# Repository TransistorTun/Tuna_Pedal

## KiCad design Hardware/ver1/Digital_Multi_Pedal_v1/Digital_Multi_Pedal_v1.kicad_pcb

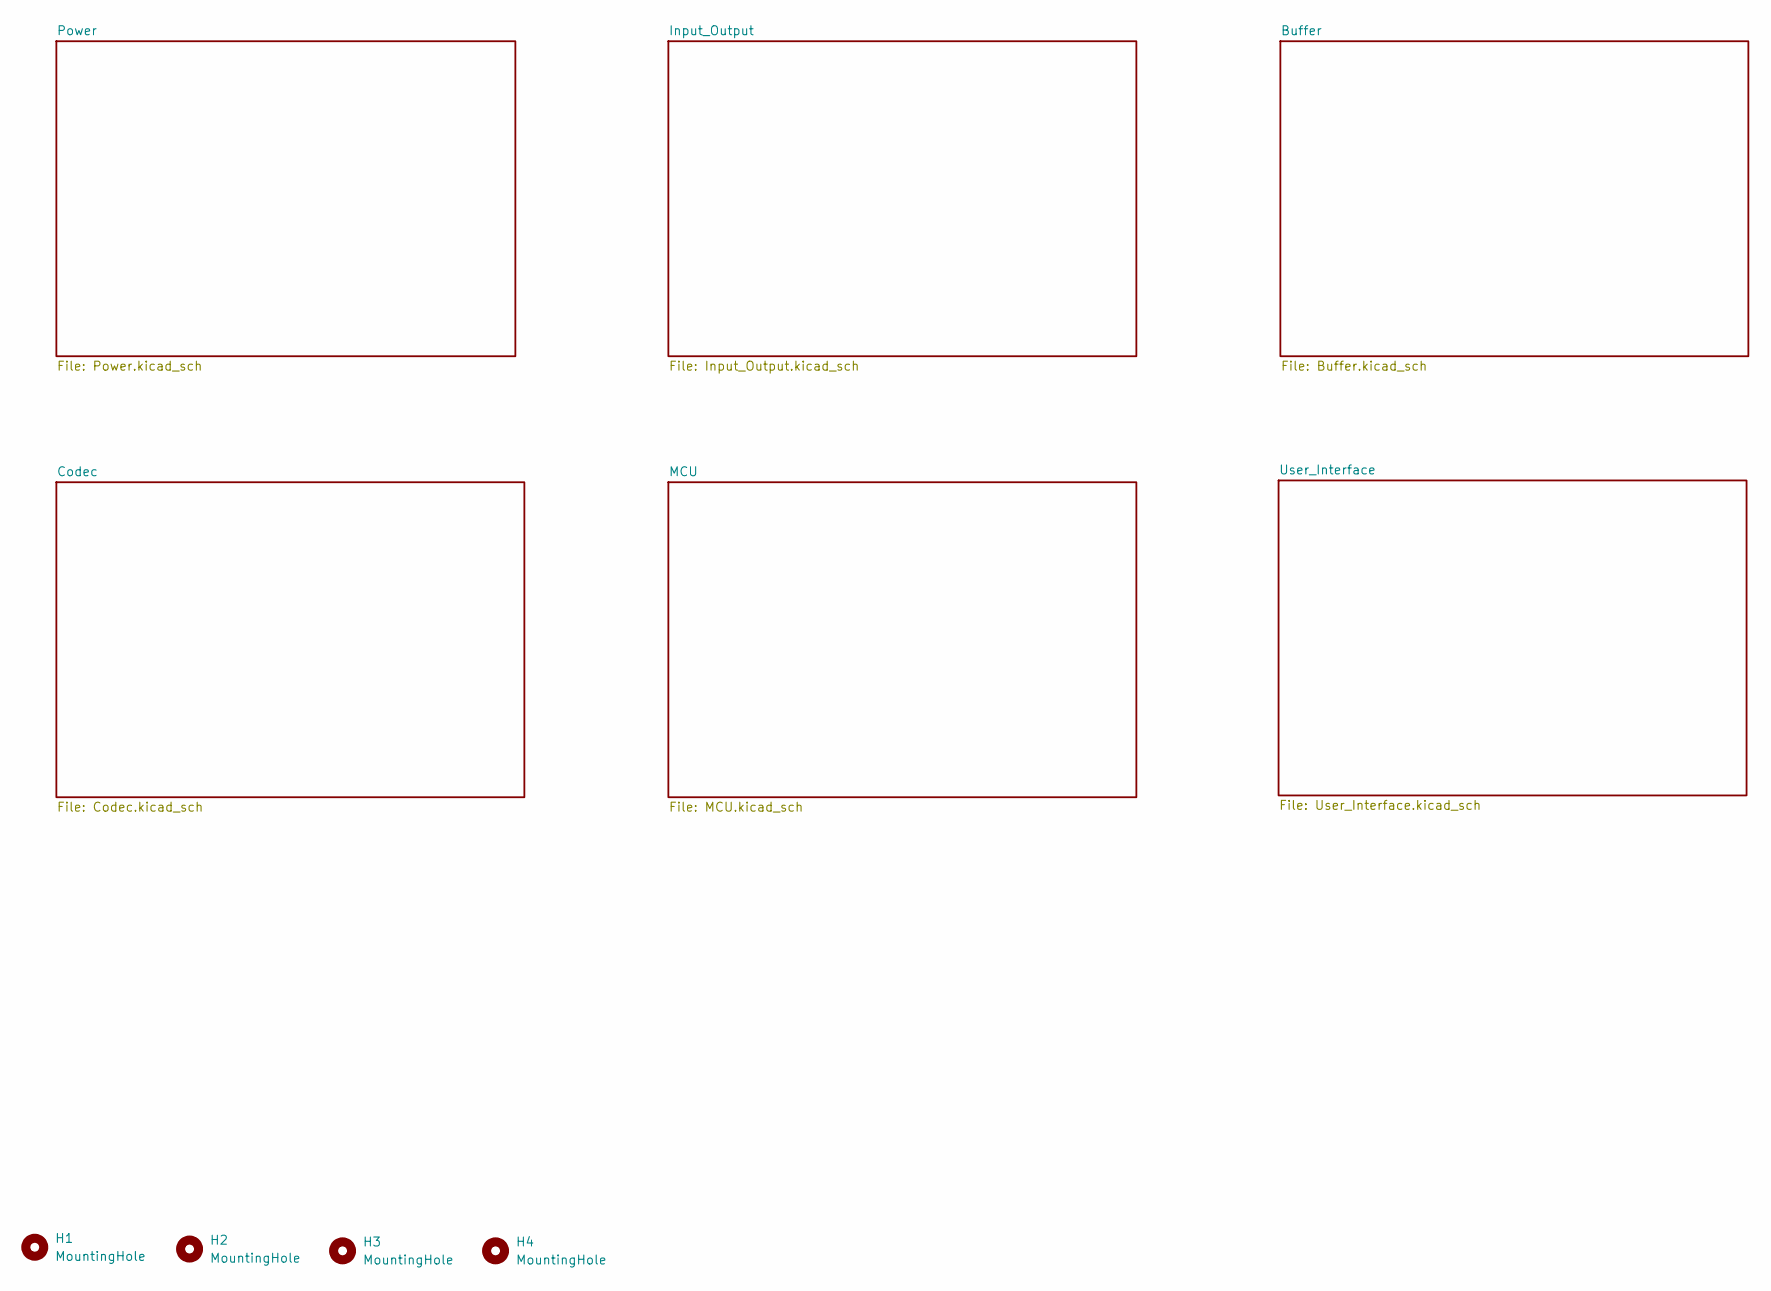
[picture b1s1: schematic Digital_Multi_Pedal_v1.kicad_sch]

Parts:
H1, H2, H3, H4: MountingHole; MountingHole_3.2mm_M3_Pad_Via

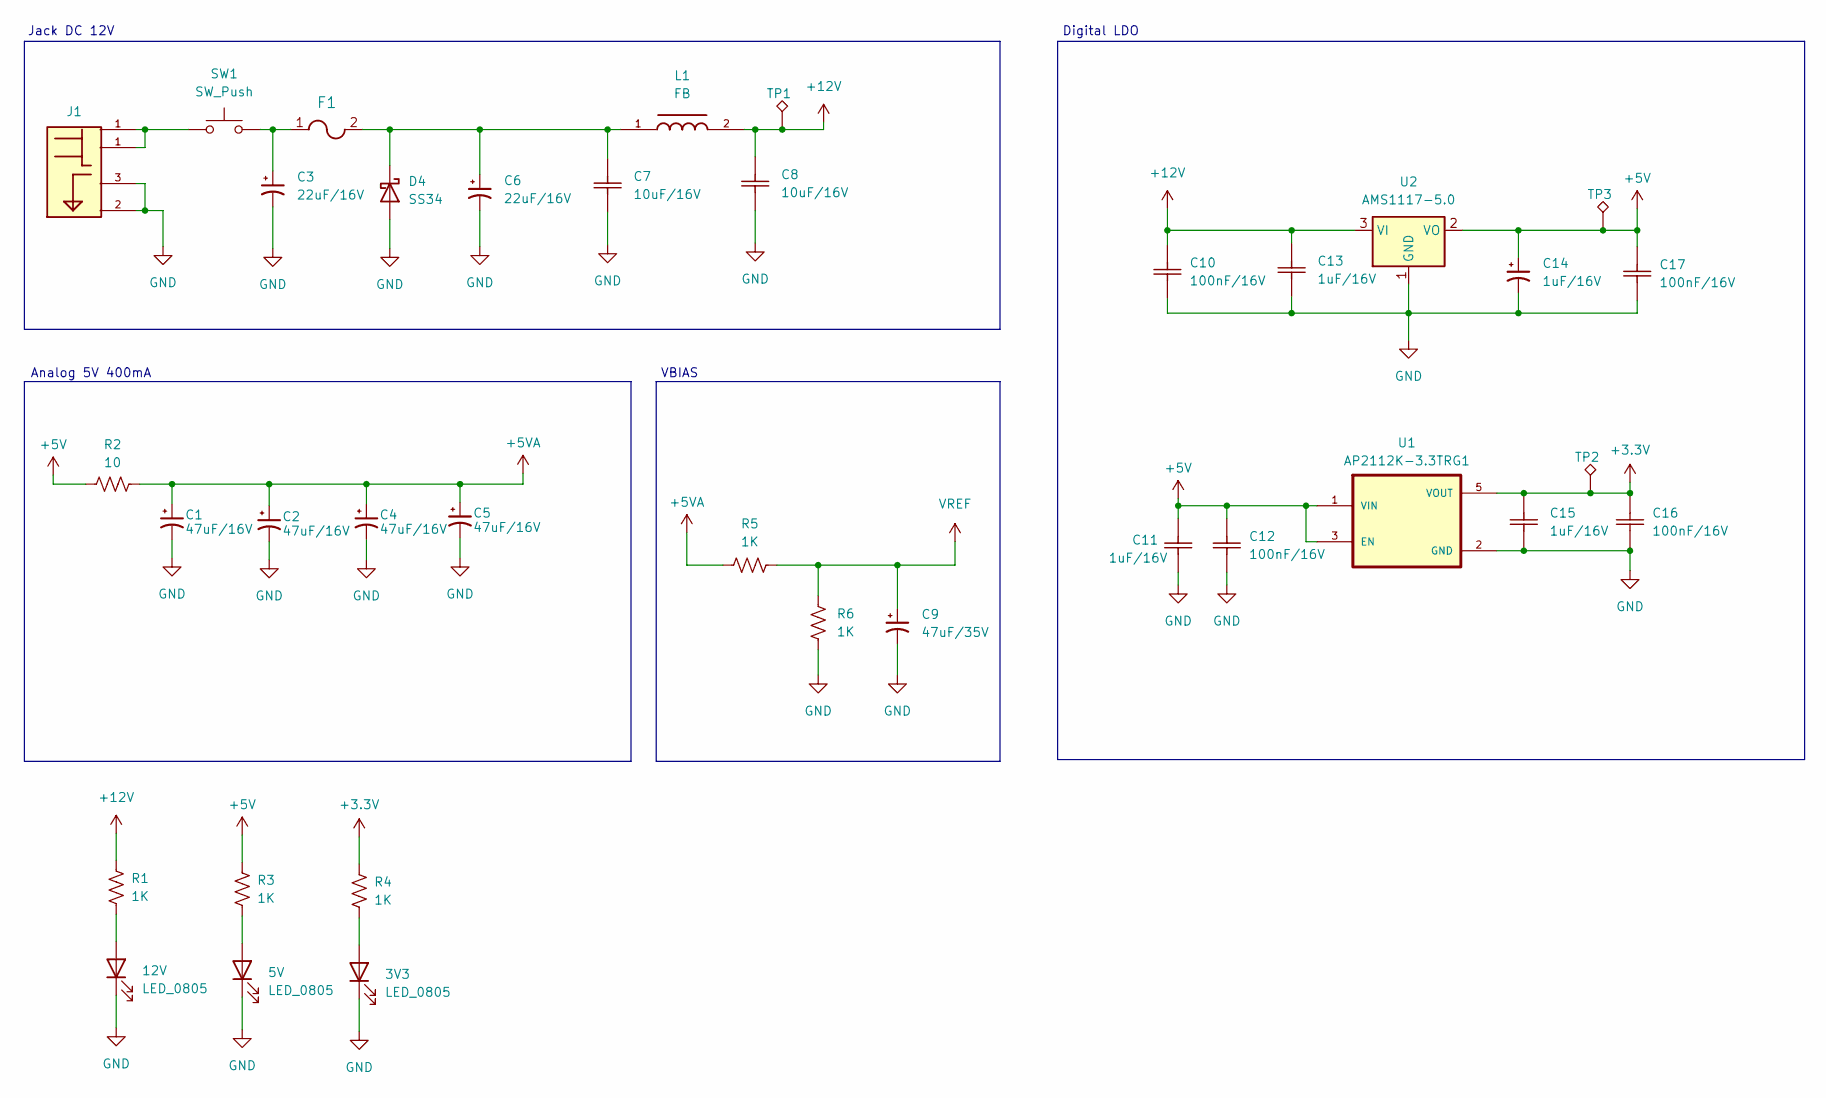
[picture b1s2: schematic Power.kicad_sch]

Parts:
3V3, 5V, 12V: LED_0805
C1, C2, C4, C5: 47uF/16V; Tan_Cap_C
C3, C6: 22uF/16V; Tan_Cap_A
C7, C8: 10uF/16V; Ceramic_Cap_0603
C9: 47uF/35V; Tan_Cap_C
C10, C12, C16, C17: 100nF/16V; Ceramic_Cap_0603
C11, C13, C15: 1uF/16V; Ceramic_Cap_0603
C14: 1uF/16V; Tan_Cap_A
D4: SS34; D_SMA
F1: Fuse; FUSE_1812L_LTF
J1: DCJ200-05-A-XX-X_REVA; JackDC
L1: FB; FB_0805
R1, R3, R4, R5, R6: 1K; Res_0603
R2: 10; Res_0603
SW1: SW_Push; Header_PW_Switch
TP1, TP2, TP3: TestPoint_Alt; TestPoint_Pad_D1.5mm
U1: AP2112K-3.3TRG1; SOT23; PARTREV 2-2
U2: AMS1117-5.0; SOT-223-3_TabPin2

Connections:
+3.3V: C15.2, C16.2, R4.1, TP2.1, U1.5 (VOUT); also elsewhere on the board
+5V: C11.2, C12.2, C14.1, C17.2, R2.2, R3.1, TP3.1, U1.1 (VIN), U1.3 (EN), U2.2 (VO); also elsewhere on the board
+5VA: C1.1, C2.1, C4.1, C5.1, R2.1, R5.2; also elsewhere on the board
+12V: C8.2, C10.2, C13.2, L1.2, R1.1, TP1.1, U2.3 (VI)
GND: 3V3.1 (K), 5V.1 (K), 12V.1 (K), C1.2, C2.2, C3.2, C4.2, C5.2, C6.2, C7.1, C8.1, C9.2, C10.1, C11.1, C12.1, C13.1, C14.2, C15.1, C16.1, C17.1, D4.2 (A), J1.2, J1.3, R6.1, U1.2 (GND), U2.1 (GND); also elsewhere on the board
unnamed: C3.1, F1.1, SW1.2
unnamed: 12V.2 (A), R1.2
unnamed: 5V.2 (A), R3.2
unnamed: 3V3.2 (A), R4.2
unnamed: C6.1, C7.2, D4.1 (K), F1.2, L1.1
unnamed: J1.1, SW1.1
VREF: C9.1, R5.1, R6.2; also elsewhere on the board

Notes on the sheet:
VBIAS
Jack DC 12V
Analog 5V 400mA
Digital LDO

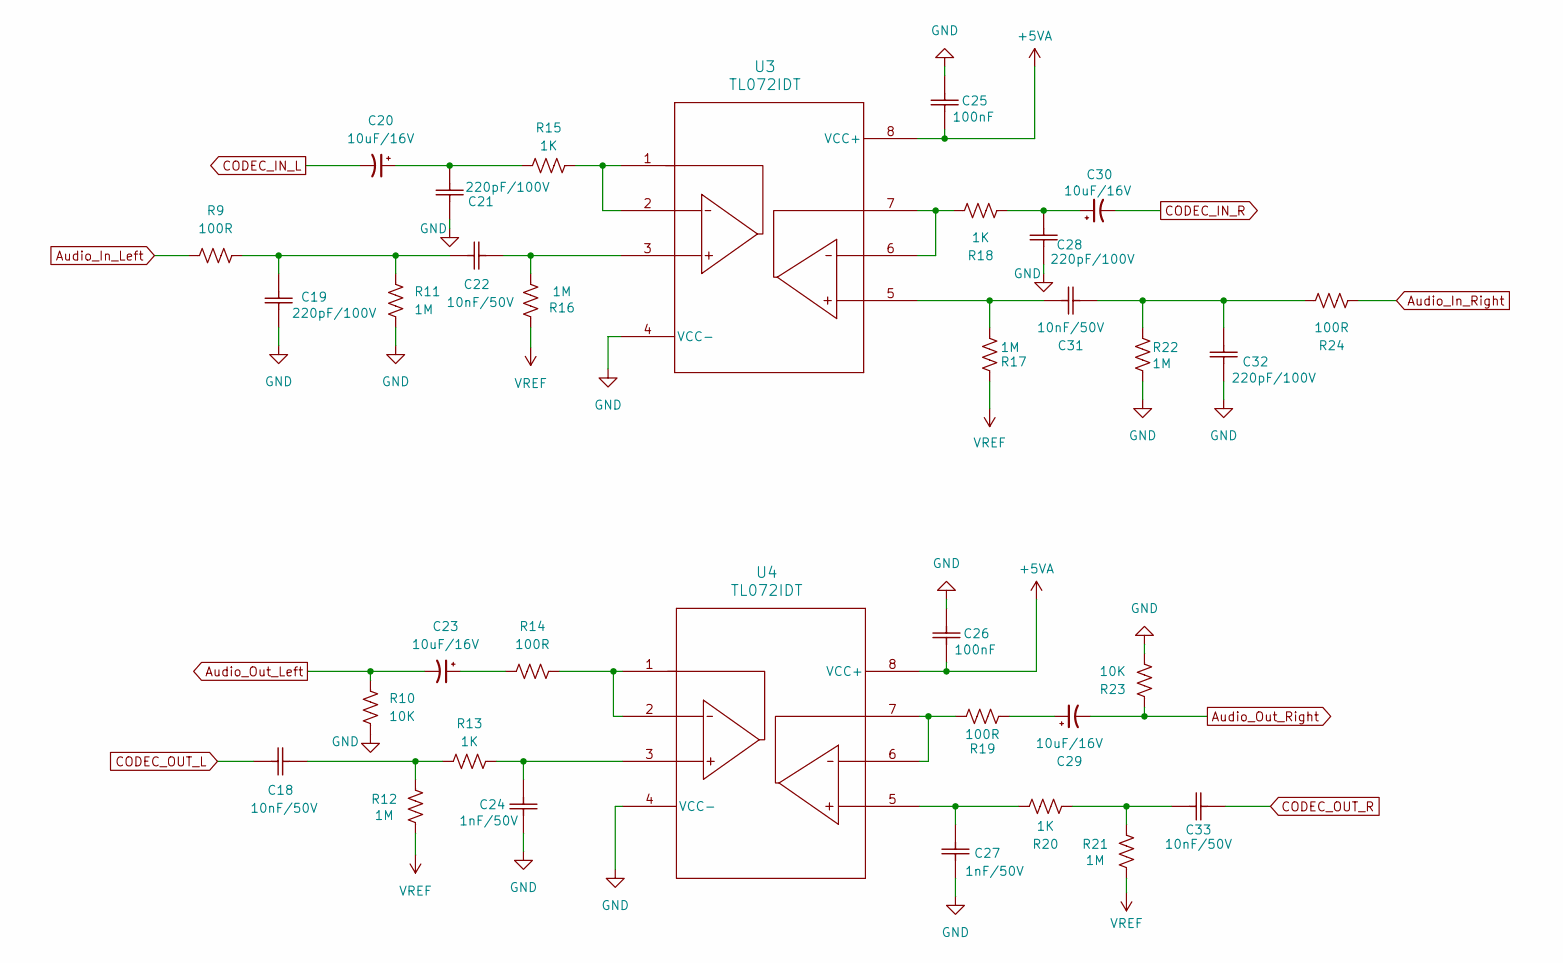
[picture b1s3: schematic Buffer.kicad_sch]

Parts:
C18, C22, C31, C33: 10nF/50V; Ceramic_Cap_0603
C19, C21, C28, C32: 220pF/100V; Ceramic_Cap_0603
C20, C23, C29, C30: 10uF/16V; Tan_Cap_A
C24, C27: 1nF/50V; Ceramic_Cap_0603
C25, C26: 100nF; Ceramic_Cap_0603
R9, R14, R19, R24: 100R; Res_0603
R10, R23: 10K; Res_0603
R11, R12, R16, R17, R21, R22: 1M; Res_0603
R13, R15, R18, R20: 1K; Res_0603
U3, U4: TL072IDT; D8_STM

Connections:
+5VA: C25.2, C26.2, U3.8 (VCC+), U4.8 (VCC+); also elsewhere on the board
Audio_In_Left: R9.1; also elsewhere on the board
Audio_In_Right: R24.1; also elsewhere on the board
Audio_Out_Left: C23.2, R10.2; also elsewhere on the board
Audio_Out_Right: C29.2, R23.2; also elsewhere on the board
CODEC_IN_L: C20.2; also elsewhere on the board
CODEC_IN_R: C30.2; also elsewhere on the board
CODEC_OUT_L: C18.1; also elsewhere on the board
CODEC_OUT_R: C33.1; also elsewhere on the board
GND: C19.2, C21.2, C24.1, C25.1, C26.1, C27.1, C28.2, C32.2, R10.1, R11.1, R22.1, R23.1, U3.4 (VCC-), U4.4 (VCC-); also elsewhere on the board
unnamed: C18.2, R12.2, R13.1
unnamed: C19.1, C22.1, R9.2, R11.2
unnamed: C20.1, C21.1, R15.1
unnamed: C22.2, R16.1, U3.3
unnamed: C23.1, R14.1
unnamed: C24.2, R13.2, U4.3
unnamed: C27.2, R20.2, U4.5
unnamed: C28.1, C30.1, R18.1
unnamed: C29.1, R19.1
unnamed: C31.1, C32.1, R22.2, R24.2
unnamed: C31.2, R17.1, U3.5
unnamed: C33.2, R20.1, R21.2
unnamed: R14.2, U4.1, U4.2
unnamed: R15.2, U3.1, U3.2
unnamed: R18.2, U3.6, U3.7
unnamed: R19.2, U4.6, U4.7
VREF: R12.1, R16.2, R17.2, R21.1; also elsewhere on the board

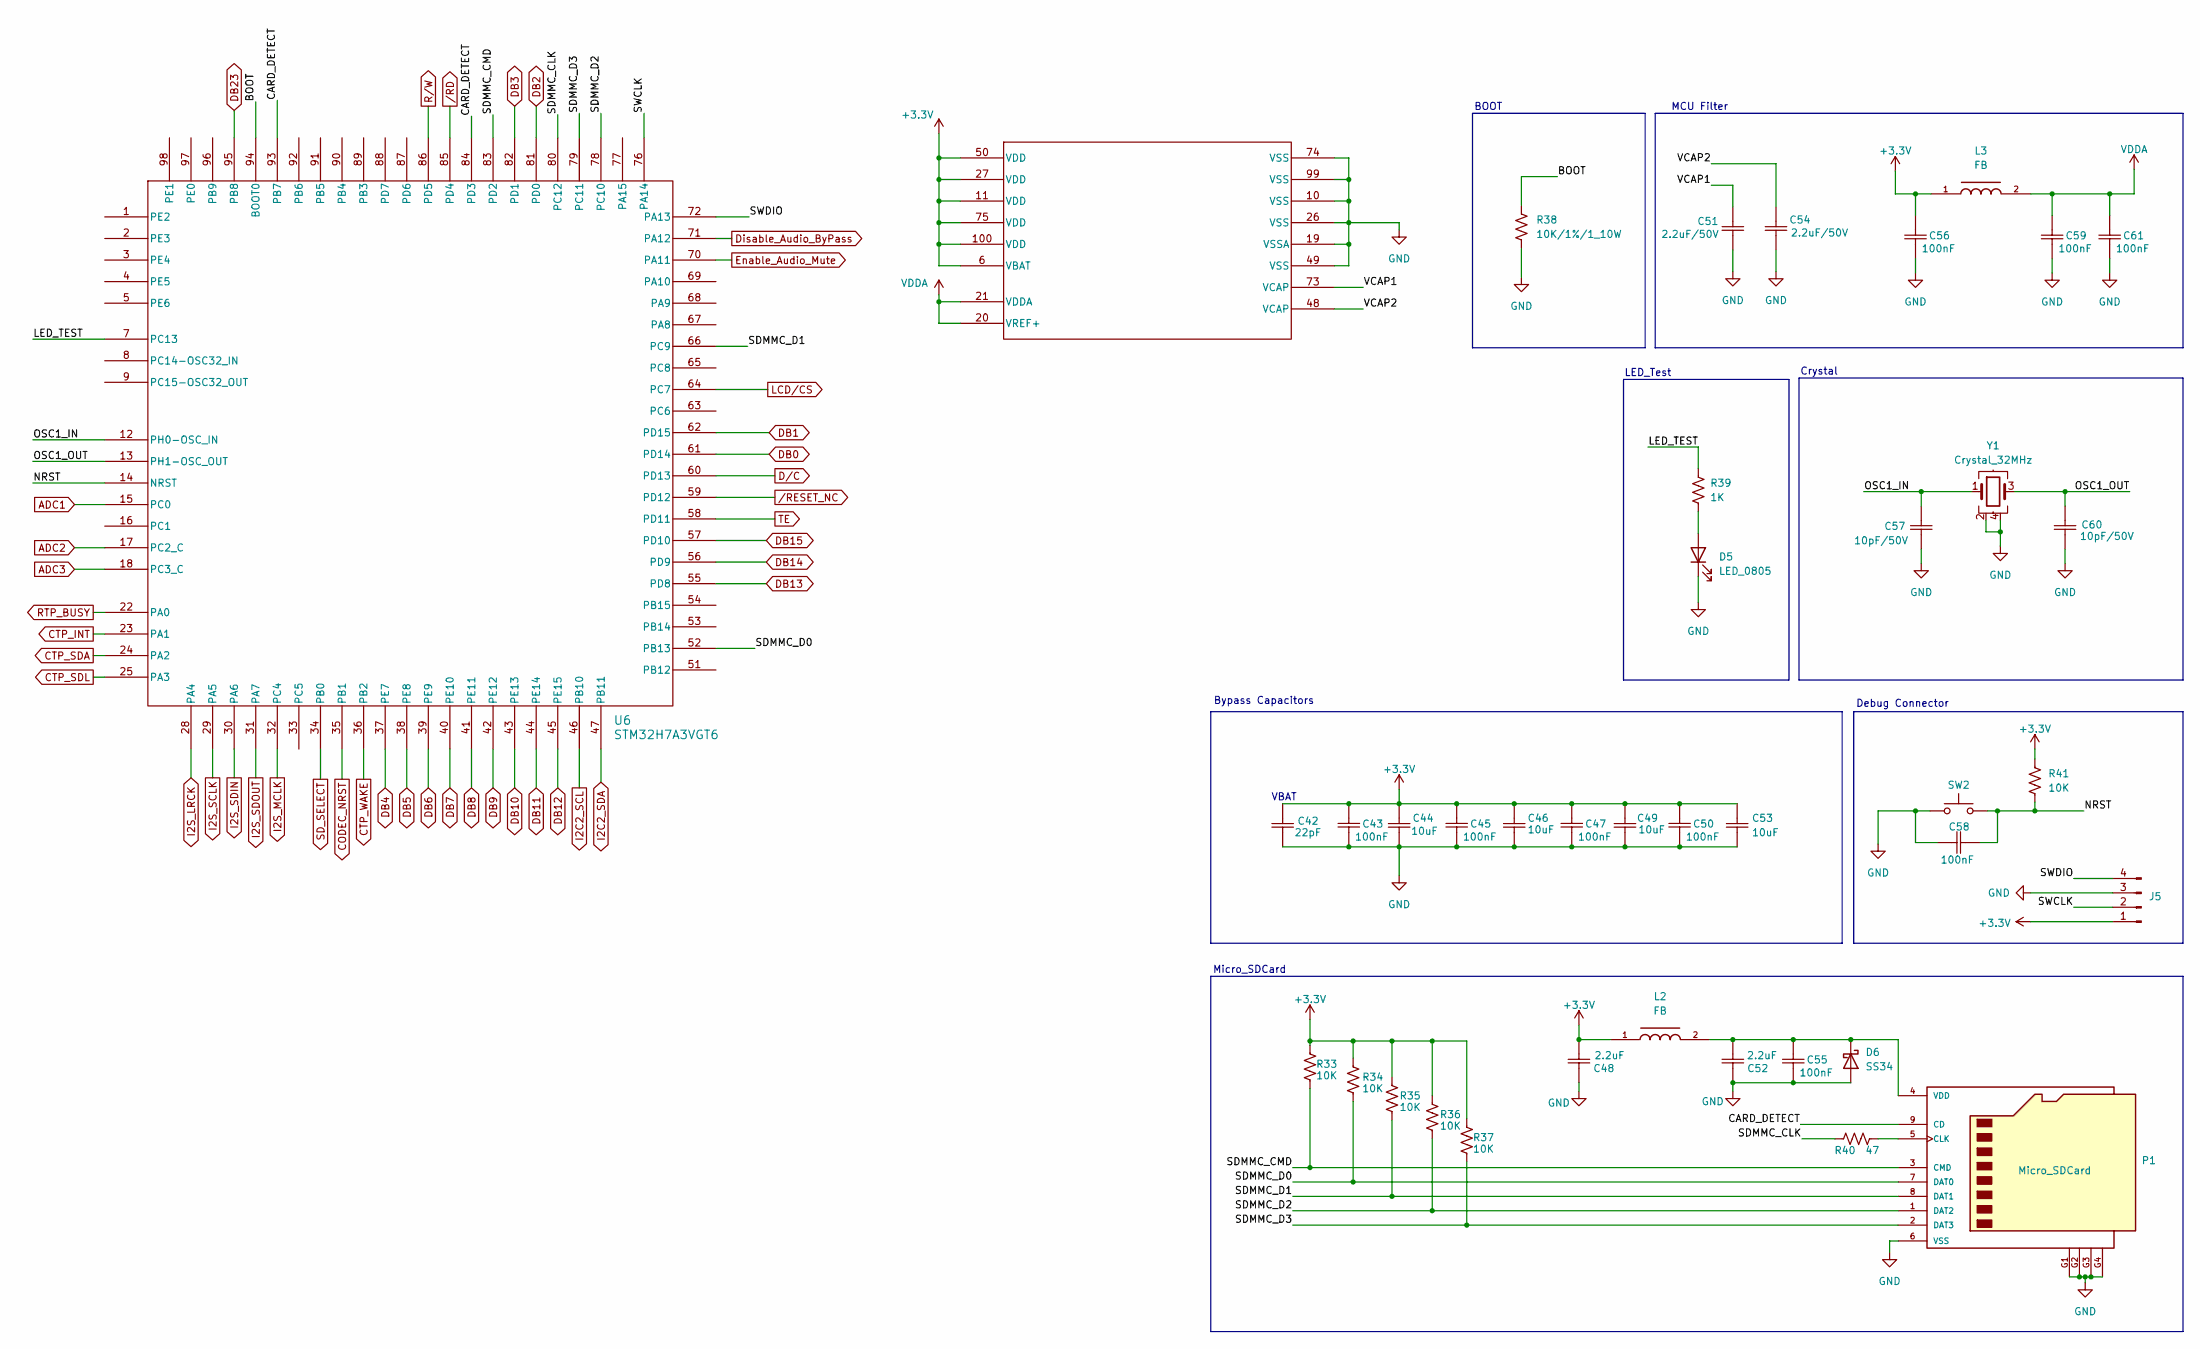
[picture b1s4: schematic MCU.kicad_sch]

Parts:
C42: 22pF; Ceramic_Cap_0603
C43, C45, C47, C50, C55, C56, C58, C59, C61: 100nF; Ceramic_Cap_0603
C44, C46, C49, C53: 10uF; Ceramic_Cap_0603
C48, C52: 2.2uF; Ceramic_Cap_0603
C51, C54: 2.2uF/50V; Ceramic_Cap_0603
C57, C60: 10pF/50V; Ceramic_Cap_0603
D5: LED_0805
D6: SS34; D_SMA
J5: PinHeader_1x04_P2.54mm_Horizontal
L2, L3: FB; FB_0805
P1: Micro_SDCard; SD_Card
R33, R34, R35, R36, R37, R41: 10K; Res_0603
R38: 10K/1%/1_10W; Res_0603
R39: 1K; Res_0603
R40: 47; Res_0402
SW2: SW_SMD
U6: STM32H7A3VGT6; STM32
Y1: Crystal_32MHz; XTAL_TSX-3225_16.0000MF18X-AC3

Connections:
+3.3V: C42.2, C43.1, C44.2, C45.1, C46.2, C47.1, C48.1, C49.2, C50.1, C53.2, C56.1, J5.1, L2.1, L3.1, R33.2, R34.2, R35.2, R36.2, R37.2, R41.2, U6.6 (VBAT), U6.11 (VDD), U6.27 (VDD), U6.50 (VDD), U6.75 (VDD), U6.100 (VDD); also elsewhere on the board
/MCU/BOOT: R38.2, U6.94 (BOOT0)
/MCU/CARD_DETECT: P1.9 (CD), U6.84 (PD3), U6.93 (PB7)
/MCU/LED_TEST: R39.1, U6.7 (PC13)
/MCU/NRST: C58.1, R41.1, SW2.2, U6.14 (NRST)
/MCU/OSC1_IN: C57.1, U6.12 (PH0-OSC_IN), Y1.1
/MCU/OSC1_OUT: C60.1, U6.13 (PH1-OSC_OUT), Y1.3
/MCU/SDMMC_CLK: R40.1, U6.80 (PC12)
/MCU/SDMMC_CMD: P1.3 (CMD), R33.1, U6.83 (PD2)
/MCU/SDMMC_D0: P1.7 (DAT0), R34.1, U6.52 (PB13)
/MCU/SDMMC_D1: P1.8 (DAT1), R35.1, U6.66 (PC9)
/MCU/SDMMC_D2: P1.1 (DAT2), R36.1, U6.78 (PC10)
/MCU/SDMMC_D3: P1.2 (DAT3), R37.1, U6.79 (PC11)
/MCU/SWCLK: J5.2, U6.76 (PA14)
/MCU/SWDIO: J5.4, U6.72 (PA13)
/MCU/VCAP1: C51.2, U6.73 (VCAP)
/MCU/VCAP2: C54.2, U6.48 (VCAP)
ADC1: U6.15 (PC0); also elsewhere on the board
ADC2: U6.17 (PC2_C); also elsewhere on the board
ADC3: U6.18 (PC3_C); also elsewhere on the board
CODEC_NRST: U6.35 (PB1); also elsewhere on the board
CTP_INT: U6.23 (PA1); also elsewhere on the board
CTP_SDA: U6.24 (PA2); also elsewhere on the board
CTP_SDL: U6.25 (PA3); also elsewhere on the board
CTP_WAKE: U6.36 (PB2); also elsewhere on the board
DB0: U6.61 (PD14); also elsewhere on the board
DB1: U6.62 (PD15); also elsewhere on the board
DB2: U6.81 (PD0); also elsewhere on the board
DB3: U6.82 (PD1); also elsewhere on the board
DB4: U6.37 (PE7); also elsewhere on the board
DB5: U6.38 (PE8); also elsewhere on the board
DB6: U6.39 (PE9); also elsewhere on the board
DB7: U6.40 (PE10); also elsewhere on the board
DB8: U6.41 (PE11); also elsewhere on the board
DB9: U6.42 (PE12); also elsewhere on the board
DB10: U6.43 (PE13); also elsewhere on the board
DB11: U6.44 (PE14); also elsewhere on the board
DB12: U6.45 (PE15); also elsewhere on the board
DB13: U6.55 (PD8); also elsewhere on the board
DB14: U6.56 (PD9); also elsewhere on the board
DB15: U6.57 (PD10); also elsewhere on the board
DB23: U6.95 (PB8)
Disable_Audio_ByPass: U6.71 (PA12)
D/C: U6.60 (PD13); also elsewhere on the board
Enable_Audio_Mute: U6.70 (PA11)
GND: C42.1, C43.2, C44.1, C45.2, C46.1, C47.2, C48.2, C49.1, C50.2, C51.1, C52.2, C53.1, C54.1, C55.2, C56.2, C57.2, C58.2, C59.2, C60.2, C61.2, D5.1 (K), D6.2 (A), J5.3, P1.6 (VSS), P1.G1, P1.G2, P1.G3, P1.G4, R38.1, SW2.1, U6.10 (VSS), U6.19 (VSSA), U6.26 (VSS), U6.49 (VSS), U6.74 (VSS), U6.99 (VSS), Y1.2, Y1.4; also elsewhere on the board
I2C2_SCL: U6.46 (PB10); also elsewhere on the board
I2C2_SDA: U6.47 (PB11); also elsewhere on the board
I2S_LRCK: U6.28 (PA4); also elsewhere on the board
I2S_MCLK: U6.32 (PC4); also elsewhere on the board
I2S_SCLK: U6.29 (PA5); also elsewhere on the board
I2S_SDIN: U6.30 (PA6); also elsewhere on the board
I2S_SDOUT: U6.31 (PA7); also elsewhere on the board
LCD/CS: U6.64 (PC7); also elsewhere on the board
unnamed: D5.2 (A), R39.2
unnamed: C52.1, C55.1, D6.1 (K), L2.2, P1.4 (VDD)
unnamed: P1.5 (CLK), R40.2
RTP_BUSY: U6.22 (PA0); also elsewhere on the board
R/W: U6.86 (PD5); also elsewhere on the board
SD_SELECT: U6.34 (PB0); also elsewhere on the board
TE: U6.58 (PD11); also elsewhere on the board
VDDA: C59.1, C61.1, L3.2, U6.20 (VREF+), U6.21 (VDDA)
/RD: U6.85 (PD4); also elsewhere on the board
/RESET_NC: U6.59 (PD12); also elsewhere on the board

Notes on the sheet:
BOOT
Crystal
Debug Connector
LED_Test
VBAT
Bypass Capacitors
Micro_SDCard
MCU Filter

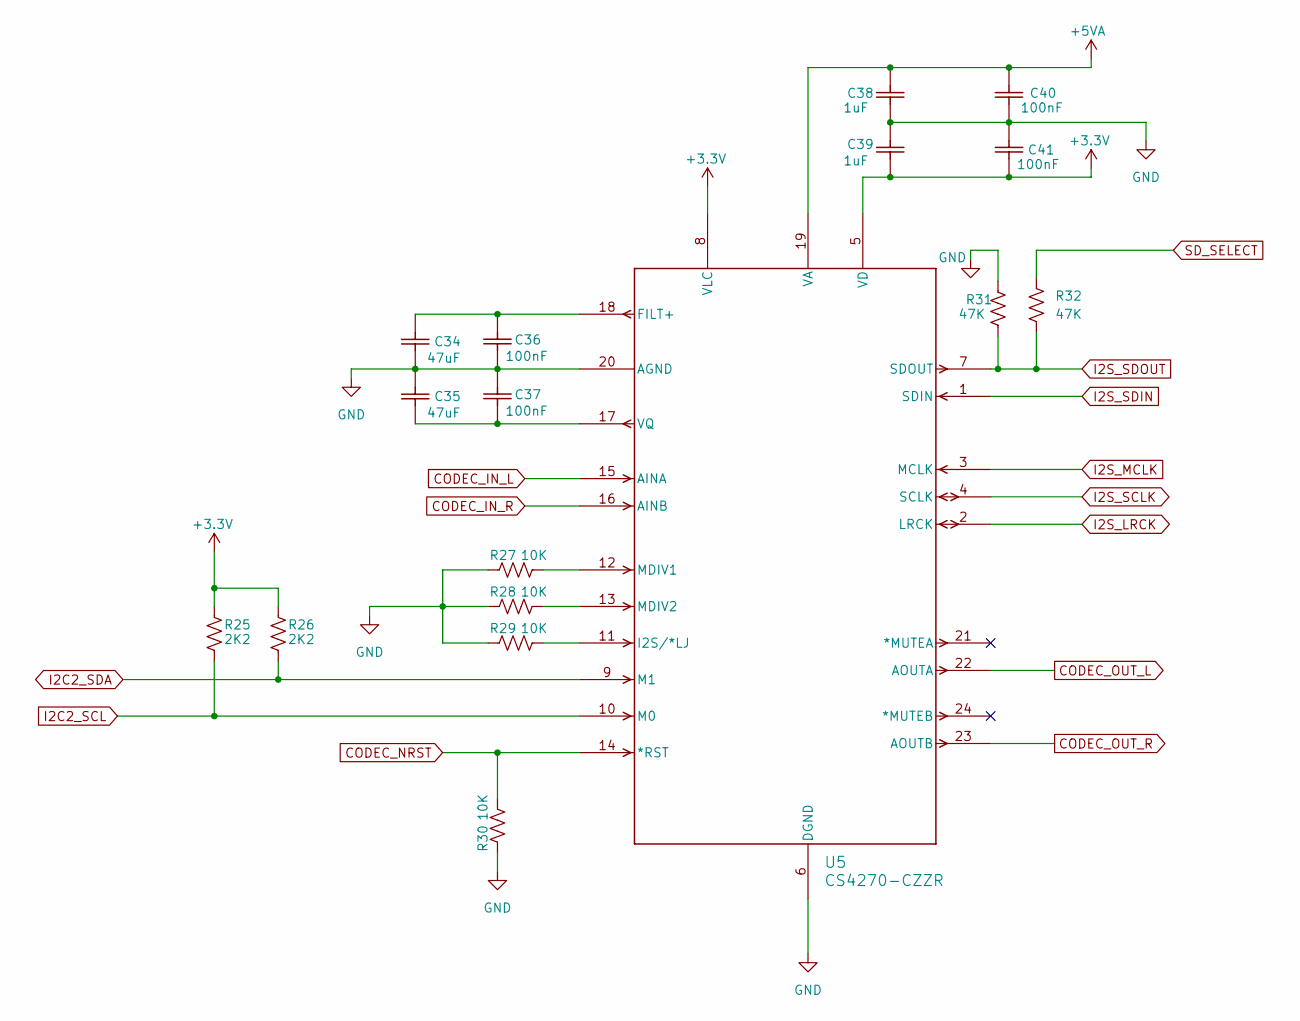
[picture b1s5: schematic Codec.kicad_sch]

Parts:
C34, C35: 47uF; Ceramic_Cap_0805
C36, C37, C40, C41: 100nF; Ceramic_Cap_0603
C38, C39: 1uF; Ceramic_Cap_0603
R25, R26: 2K2; Res_0603
R27, R28, R29, R30: 10K; Res_0603
R31, R32: 47K; Res_0603
U5: CS4270-CZZR; CIR-TSSOP-24

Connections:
+3.3V: C39.2, C41.2, R25.2, R26.2, U5.5 (VD), U5.8 (VLC); also elsewhere on the board
+5VA: C38.1, C40.1, U5.19 (VA); also elsewhere on the board
CODEC_IN_L: U5.15 (AINA); also elsewhere on the board
CODEC_IN_R: U5.16 (AINB); also elsewhere on the board
CODEC_NRST: R30.2, U5.14 (*RST); also elsewhere on the board
CODEC_OUT_L: U5.22 (AOUTA); also elsewhere on the board
CODEC_OUT_R: U5.23 (AOUTB); also elsewhere on the board
GND: C34.1, C35.2, C36.2, C37.1, C38.2, C39.1, C40.2, C41.1, R27.1, R28.1, R29.1, R30.1, R31.2, U5.6 (DGND), U5.20 (AGND); also elsewhere on the board
I2C2_SCL: R25.1, U5.10 (M0); also elsewhere on the board
I2C2_SDA: R26.1, U5.9 (M1); also elsewhere on the board
I2S_LRCK: U5.2 (LRCK); also elsewhere on the board
I2S_MCLK: U5.3 (MCLK); also elsewhere on the board
I2S_SCLK: U5.4 (SCLK); also elsewhere on the board
I2S_SDIN: U5.1 (SDIN); also elsewhere on the board
I2S_SDOUT: R31.1, R32.1, U5.7 (SDOUT); also elsewhere on the board
unnamed: C34.2, C36.1, U5.18 (FILT+)
unnamed: R29.2, U5.11 (I2S/*LJ)
unnamed: R27.2, U5.12 (MDIV1)
unnamed: R28.2, U5.13 (MDIV2)
unnamed: C35.1, C37.2, U5.17 (VQ)
SD_SELECT: R32.2; also elsewhere on the board

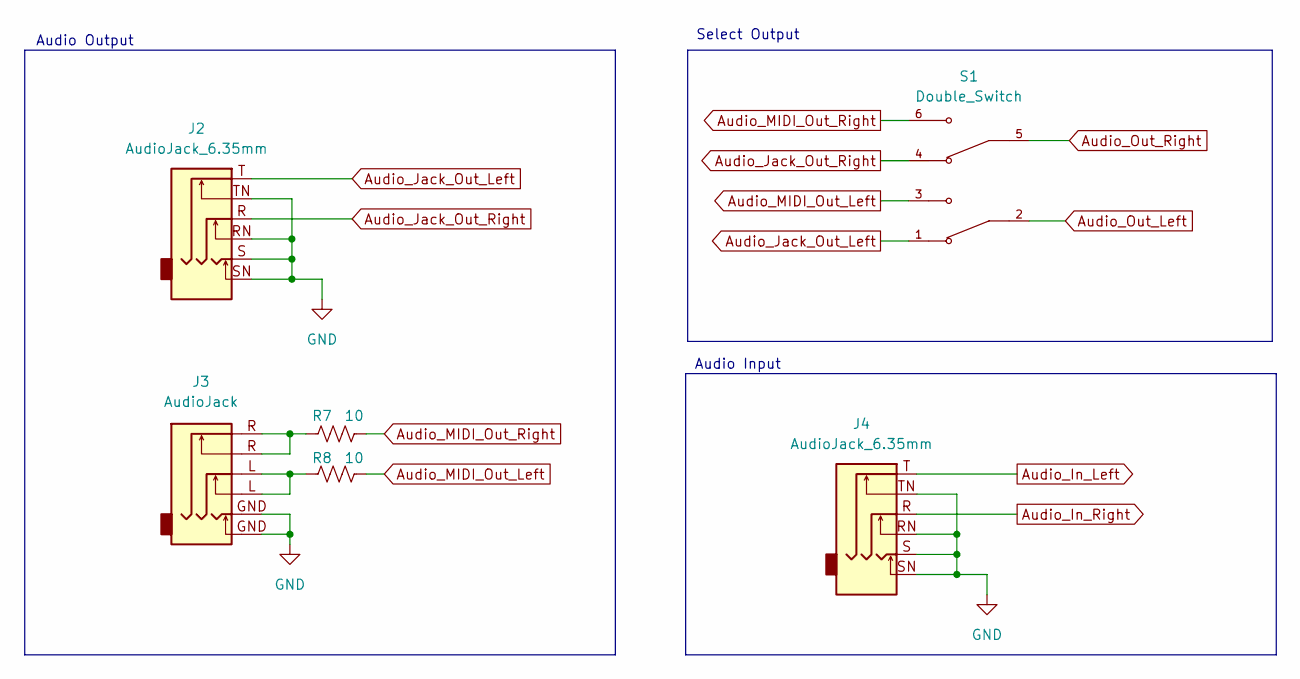
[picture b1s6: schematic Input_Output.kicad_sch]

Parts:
J2, J4: AudioJack_6.35mm; Jack_Audio_6.35mm
J3: AudioJack; Audio_connector
R7, R8: 10; Res_0603
S1: Double_Switch; PARTREV C

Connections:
Audio_In_Left: J4.T; also elsewhere on the board
Audio_In_Right: J4.R; also elsewhere on the board
Audio_Jack_Out_Left: J2.T, S1.1
Audio_Jack_Out_Right: J2.R, S1.4
Audio_MIDI_Out_Left: R8.2, S1.3
Audio_MIDI_Out_Right: R7.2, S1.6
Audio_Out_Left: S1.2; also elsewhere on the board
Audio_Out_Right: S1.5; also elsewhere on the board
GND: J2.RN, J2.S, J2.SN, J2.TN, J3.GND, J4.RN, J4.S, J4.SN, J4.TN; also elsewhere on the board
unnamed: J3.L, R8.1
unnamed: J3.R, R7.1

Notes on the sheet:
Audio Output
Select Output
Audio Input

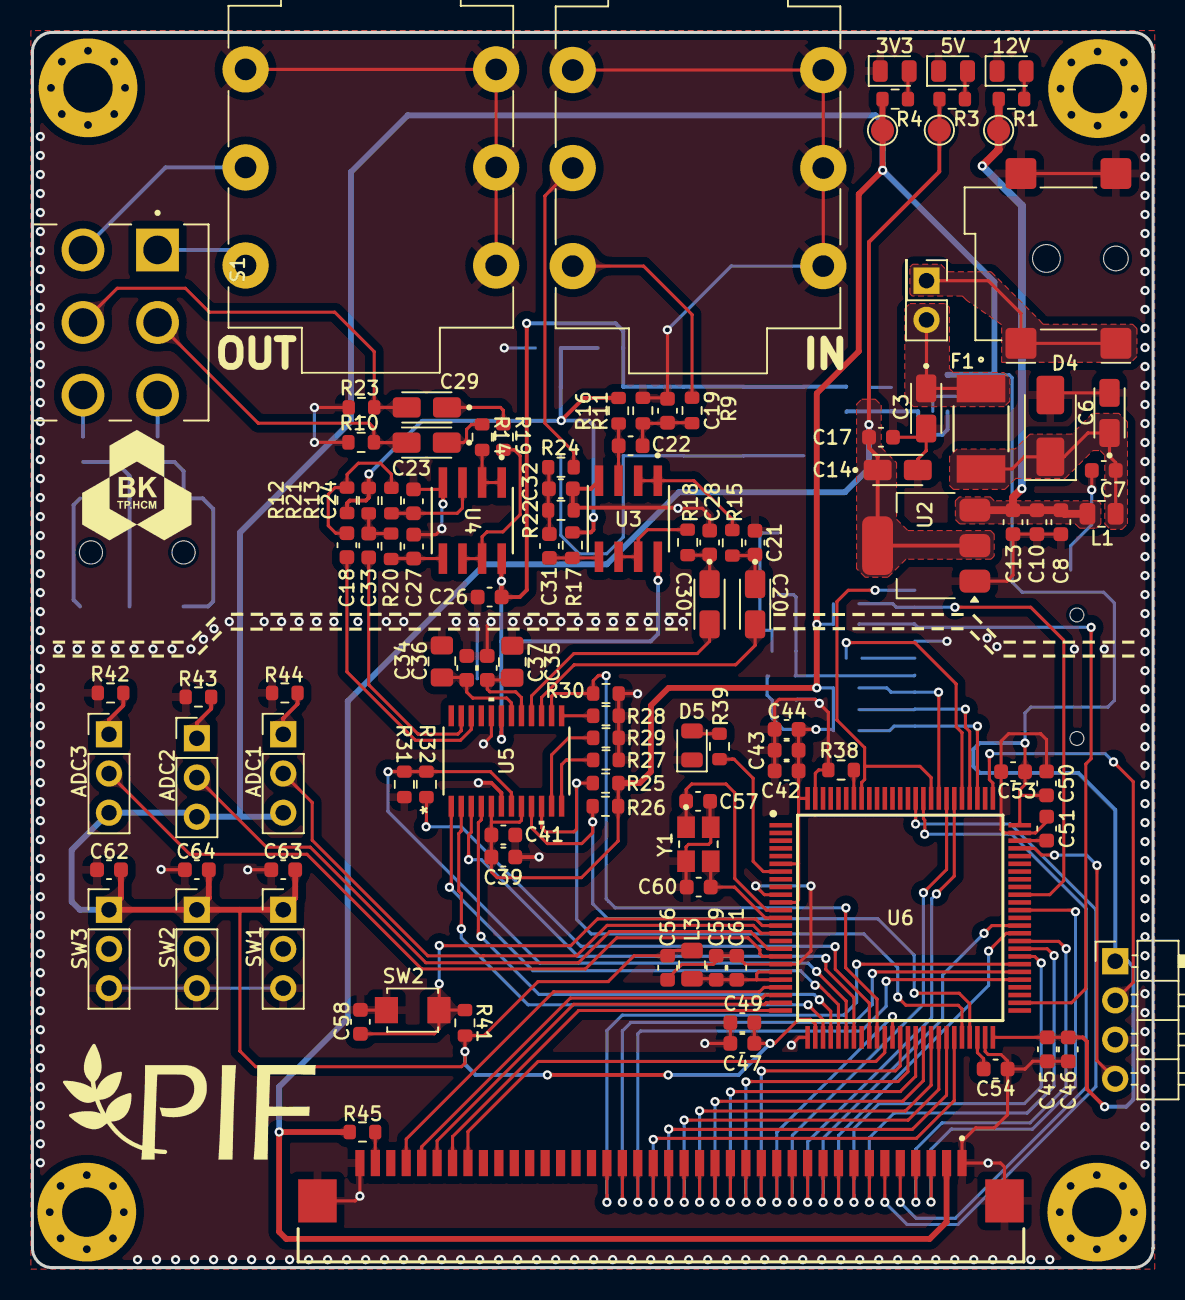
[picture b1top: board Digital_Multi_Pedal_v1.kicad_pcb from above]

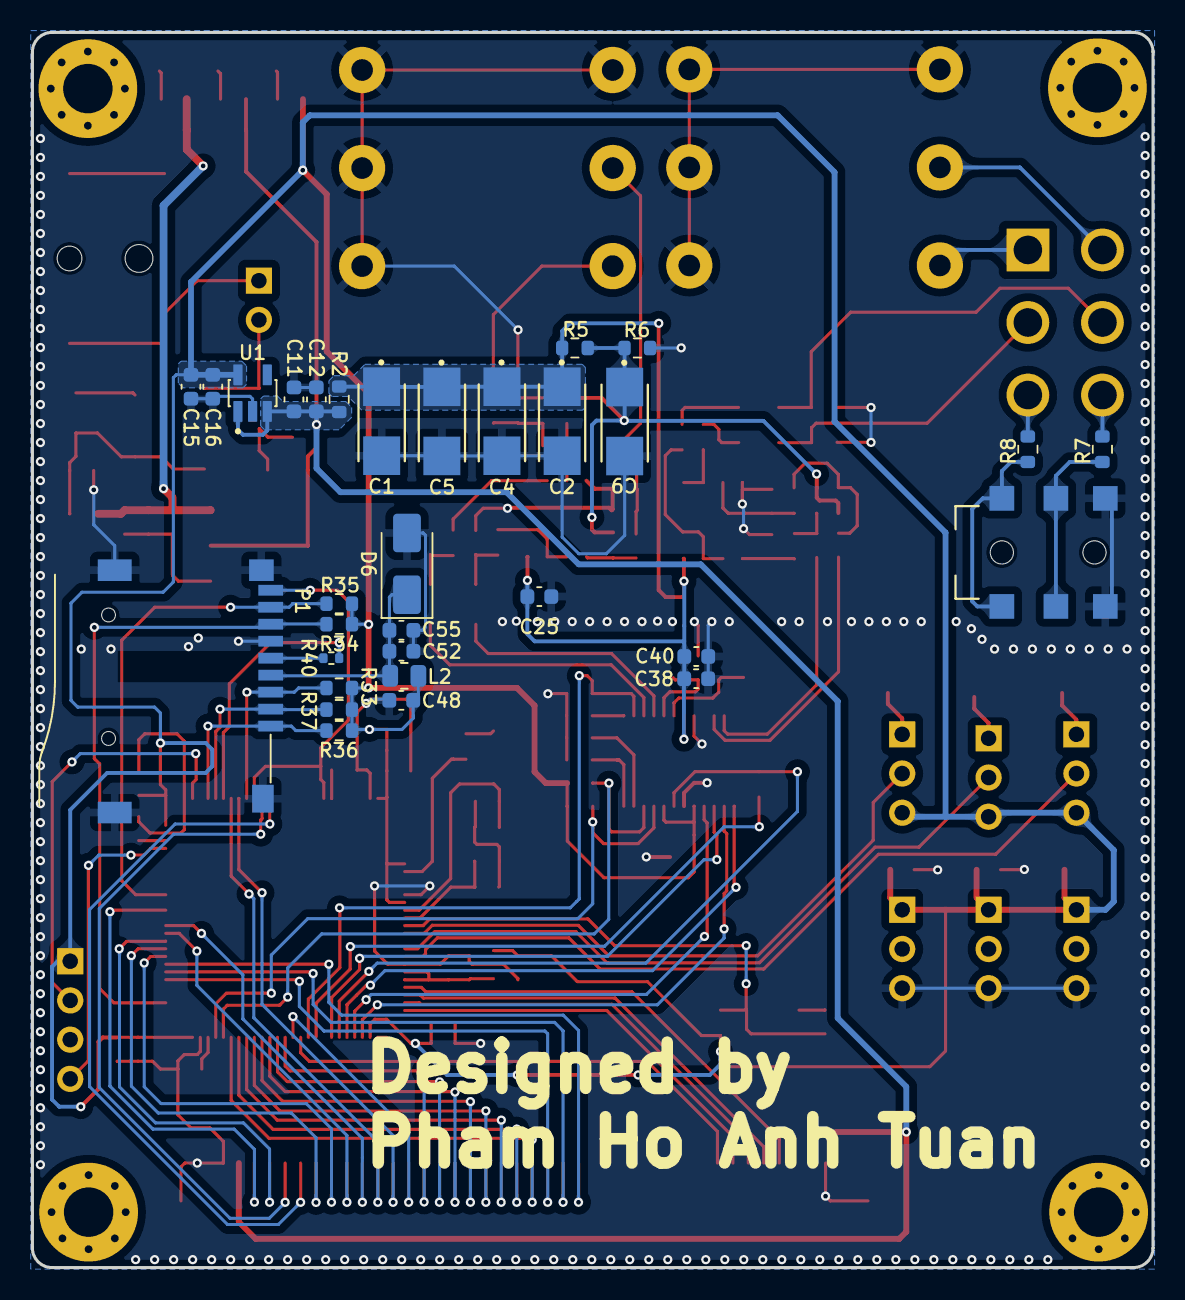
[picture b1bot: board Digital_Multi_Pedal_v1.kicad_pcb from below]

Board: 4 copper layers, 72.6 x 80.0 mm, 149 parts (31 on the bottom side), 110 nets.

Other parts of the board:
ADC1, ADC2, ADC3: VariableRes; PinHeader_1x03_P2.54mm_Vertical
C62, C63, C64: 10uF; Ceramic_Cap_0603
J9: Connector_40pin
R42, R43, R44, R45: 100R; Res_0603
SW1#2, SW2#2, SW3: Footswitch; PinHeader_1x03_P2.54mm_Vertical

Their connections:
+3.3V: ADC1.3, ADC2.3, ADC3.3, C62.2, C63.2, C64.2, SW1#2.1 (A), SW2#2.1 (A), SW3.1 (A); also elsewhere on the board
+5V: J9.2, R45.2; also elsewhere on the board
ADC1: ADC1.2; also elsewhere on the board
ADC2: ADC2.2; also elsewhere on the board
ADC3: ADC3.2; also elsewhere on the board
CTP_INT: J9.36; also elsewhere on the board
CTP_SDA: J9.35; also elsewhere on the board
CTP_SDL: J9.34; also elsewhere on the board
CTP_WAKE: J9.33; also elsewhere on the board
DB0: J9.9; also elsewhere on the board
DB1: J9.10; also elsewhere on the board
DB2: J9.11; also elsewhere on the board
DB3: J9.12; also elsewhere on the board
DB4: J9.13; also elsewhere on the board
DB5: J9.14; also elsewhere on the board
DB6: J9.15; also elsewhere on the board
DB7: J9.16; also elsewhere on the board
DB8: J9.17; also elsewhere on the board
DB9: J9.18; also elsewhere on the board
DB10: J9.19; also elsewhere on the board
DB11: J9.20; also elsewhere on the board
DB12: J9.21; also elsewhere on the board
DB13: J9.22; also elsewhere on the board
DB14: J9.23; also elsewhere on the board
DB15: J9.24; also elsewhere on the board
D/C: J9.4; also elsewhere on the board
GND: C62.1, C63.1, C64.1, J9.1, J9.40, J9.S1 (SHIELD), J9.S2 (SHIELD), R42.1, R43.1, R44.1, SW1#2.3 (C), SW2#2.3 (C), SW3.3 (C); also elsewhere on the board
LCD/CS: J9.3; also elsewhere on the board
unnamed: J9.39, R45.1
unnamed: ADC3.1, R42.2
unnamed: ADC2.1, R43.2
unnamed: ADC1.1, R44.2
RTP_BUSY: J9.37; also elsewhere on the board
R/W: J9.6; also elsewhere on the board
TE: J9.8; also elsewhere on the board
/RD: J9.5; also elsewhere on the board
/RESET_NC: J9.7; also elsewhere on the board

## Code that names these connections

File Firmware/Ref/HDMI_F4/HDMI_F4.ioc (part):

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Mcu.Name=STM32F407V(E-G)Tx
Mcu.Package=LQFP100
Mcu.UserName=STM32F407VGTx
PA11.Mode=Device_Only
PA11.Signal=USB_OTG_FS_DM
PA12.Mode=Device_Only
PA12.Signal=USB_OTG_FS_DP
PA13.Mode=Serial_Wire
PA13.Signal=SYS_JTMS-SWDIO
PA14.Mode=Serial_Wire
PA14.Signal=SYS_JTCK-SWCLK
PA15.GPIOParameters=GPIO_Speed,PinState,GPIO_Label
PA15.GPIO_Label=SD_CS
PA15.GPIO_Speed=GPIO_SPEED_FREQ_VERY_HIGH
PA15.PinState=GPIO_PIN_SET
PA15.Signal=GPIO_Output
PA2.GPIOParameters=GPIO_PuPd
PA2.GPIO_PuPd=GPIO_PULLUP
PA2.Mode=Asynchronous
PA2.Signal=USART2_TX
PA3.GPIOParameters=GPIO_PuPd
PA3.GPIO_PuPd=GPIO_PULLUP
PA3.Mode=Asynchronous
PA3.Signal=USART2_RX
PA4.GPIOParameters=GPIO_Speed,PinState,GPIO_Label
PA4.GPIO_Label=ROM_CS
PA4.GPIO_Speed=GPIO_SPEED_FREQ_VERY_HIGH
PA4.PinState=GPIO_PIN_SET
PA4.Signal=GPIO_Output
PA5.Mode=Full_Duplex_Master
PA5.Signal=SPI1_SCK
PA6.Mode=Full_Duplex_Master
PA6.Signal=SPI1_MISO
PA7.Mode=Full_Duplex_Master
PA7.Signal=SPI1_MOSI
PB0.GPIOParameters=GPIO_Speed,GPIO_Label
PB0.GPIO_Label=CTP_RST
PB0.GPIO_Speed=GPIO_SPEED_FREQ_HIGH
PB0.Signal=GPIO_Output
PB1.GPIOParameters=GPIO_Speed,GPIO_Label
PB1.GPIO_Label=CTP_INT
PB1.GPIO_Speed=GPIO_SPEED_FREQ_HIGH
PB1.Signal=GPIO_Output
PB7.GPIOParameters=GPIO_Pu
PB7.GPIO_Pu=GPIO_PULLUP
PB7.Mode=I2C
PB7.Signal=I2C1_SDA
PB8.GPIOParameters=GPIO_Pu
PB8.GPIO_Pu=GPIO_PULLUP
PB8.Mode=I2C
PB8.Signal=I2C1_SCL
PB9.GPIOParameters=GPIO_Label
PB9.GPIO_Label=LED
PB9.Signal=GPIO_Output
PC10.GPIOParameters=GPIO_Speed,GPIO_PuPd
PC10.GPIO_PuPd=GPIO_NOPULL
PC10.GPIO_Speed=GPIO_SPEED_FREQ_VERY_HIGH
PC10.Mode=Full_Duplex_Master
PC10.Signal=SPI3_SCK
PC11.GPIOParameters=GPIO_PuPd
PC11.GPIO_PuPd=GPIO_NOPULL
PC11.Mode=Full_Duplex_Master
PC11.Signal=SPI3_MISO
PC12.GPIOParameters=GPIO_PuPd
PC12.GPIO_PuPd=GPIO_NOPULL
PC12.Mode=Full_Duplex_Master
PC12.Signal=SPI3_MOSI
PC7.GPIOParameters=GPIO_Speed
PC7.GPIO_Speed=GPIO_SPEED_FREQ_HIGH
PC7.Signal=GPIO_Output
PC8.GPIOParameters=GPIO_PuPd,GPIO_Label
PC8.GPIO_Label=SD_DETECT 
PC8.GPIO_PuPd=GPIO_PULLUP
PC8.Signal=GPIO_Input
PD0.Mode=16b-d1
PD0.Signal=FSMC_D2
PD1.Mode=16b-d1
PD1.Signal=FSMC_D3
PD10.Mode=16b-d1
PD10.Signal=FSMC_D15
PD11.Mode=A16_1
PD11.Signal=FSMC_A16
PD14.Mode=16b-d1
PD14.Signal=FSMC_D0
PD15.Mode=16b-d1
PD15.Signal=FSMC_D1
PD4.Mode=Lcd1
PD4.Signal=FSMC_NOE
PD5.Mode=Lcd1
PD5.Signal=FSMC_NWE
PD6.GPIOParameters=GPIO_Speed,PinState,GPIO_Label
PD6.GPIO_Label=TFT_RESET
PD6.GPIO_Speed=GPIO_SPEED_FREQ_VERY_HIGH
PD6.PinState=GPIO_PIN_SET
PD6.Signal=GPIO_Output
PD7.Mode=NorPsramChipSelect1_1
PD7.Signal=FSMC_NE1
PD8.Mode=16b-d1
PD8.Signal=FSMC_D13
PD9.Mode=16b-d1
PD9.Signal=FSMC_D14
PE0.GPIOParameters=GPIO_PuPd,GPIO_Label
PE0.GPIO_Label=POWER_SW
PE0.GPIO_PuPd=GPIO_PULLUP
PE0.Signal=GPIO_Input
PE1.GPIOParameters=PinState,GPIO_Label
PE1.GPIO_Label=POWER_ON
PE1.PinState=GPIO_PIN_SET
PE1.Signal=GPIO_Output
PE10.Mode=16b-d1
PE10.Signal=FSMC_D7
PE11.Mode=16b-d1
PE11.Signal=FSMC_D8
PE12.Mode=16b-d1
PE12.Signal=FSMC_D9
PE13.Mode=16b-d1
PE13.Signal=FSMC_D10
PE14.Mode=16b-d1
PE14.Signal=FSMC_D11
PE15.Mode=16b-d1
PE15.Signal=FSMC_D12
PE7.Mode=16b-d1
PE7.Signal=FSMC_D4
PE8.Mode=16b-d1
PE8.Signal=FSMC_D5
PE9.Mode=16b-d1
PE9.Signal=FSMC_D6
PH0-OSC_IN.Mode=HSE-External-Oscillator
PH0-OSC_IN.Signal=RCC_OSC_IN
PH1-OSC_OUT.Mode=HSE-External-Oscillator
PH1-OSC_OUT.Signal=RCC_OSC_OUT
RCC.HSE_VALUE=25000000
RCC.SYSCLKFreq_VALUE=168000000
RCC.SYSCLKSource=RCC_SYSCLKSOURCE_PLLCLK
board=custom

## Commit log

2025-02-17 init github for my project
